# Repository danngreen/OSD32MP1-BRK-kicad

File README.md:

## OSD32MP1-BRK Kicad project

This is a Kicad project for the OSD32MP1-BRK breakout board from Octavo Systems. 
It requires Kicad v5.99 or later (aka Kicad 6). 

I converted the Altium project files for this board as best I could, using Kicad's built-in Altium importer.
The Kicad project here passes ERC and DRC, and has sane project settings (track thickness, clearance, etc.). You can view the steps I had to take to manually correct the automatic import script by viewing the git commit log.

The symbols and footprints are all extracted from the Altium project.

There are some minor font differences on the silk-screen layers, and the zones may have different clearances. I do not have access to the original gerbers, so I haven't compared them.
I have not produced this board (nor do I intend to), so I don't know if it even works.

#### Disclaimer:
I am in no way associated with Octavo Systems, and the files in this repository may contain errors or have issues, so I make no warranty as to anything. I also make no claims to ownership.
I believe I am allowed to publish this under the same license as the original files, but if I am incorrect then I will remove this repository.

The OSD32MP1-BRK Altium files are available on Octavo Systems website [here](https://octavosystems.com/octavo_products/osd32mp1-brk/#Design%20Files).

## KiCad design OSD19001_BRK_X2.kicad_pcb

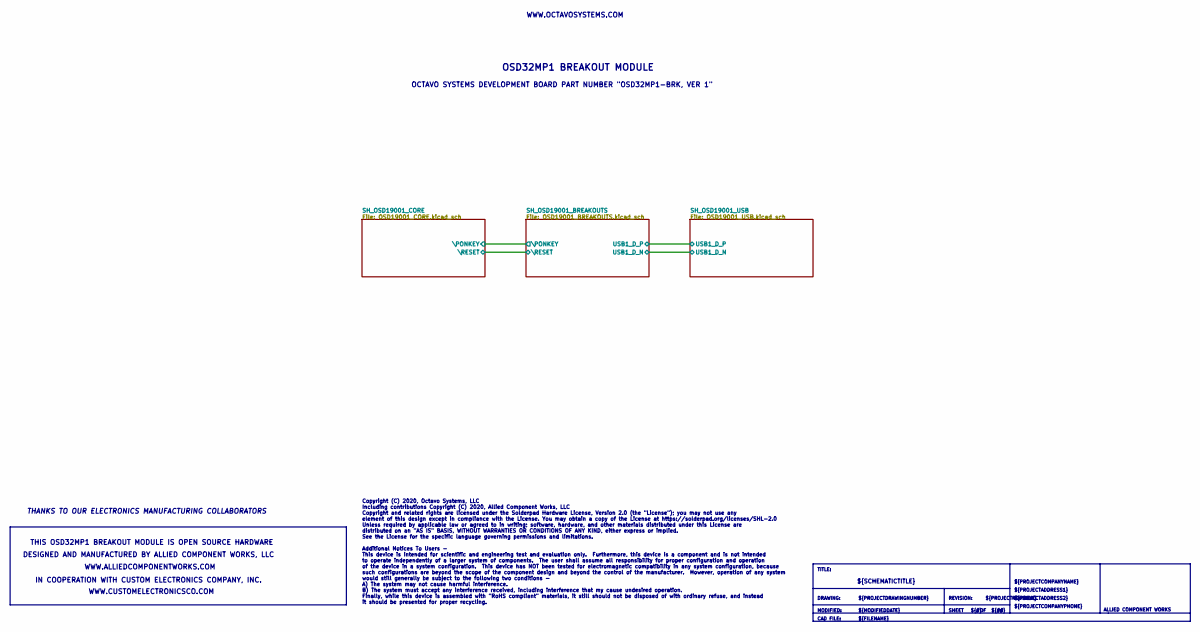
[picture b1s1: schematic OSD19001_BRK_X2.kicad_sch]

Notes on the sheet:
DESIGNED AND MANUFACTURED BY ALLIED COMPONENT WORKS, LLC
THANKS TO OUR ELECTRONICS MANUFACTURING COLLABORATORS
THIS OSD32MP1 BREAKOUT MODULE IS OPEN SOURCE HARDWARE
IN COOPERATION WITH CUSTOM ELECTRONICS COMPANY, INC.
WWW.ALLIEDCOMPONENTWORKS.COM
WWW.CUSTOMELECTRONICSCO.COM
Copyright (C) 2020, Octavo Systems, LLC Including contributions Copyright (C) 2020, Allied Component Works, LLC Copyright and related rights are licensed under the Solderpad Hardware License, Version 2.0 (the "License"); you may not use any element of this design except in compliance with the Licen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
OCTAVO SYSTEMS DEVELOPMENT BOARD PART NUMBER "OSD32MP1-BRK, VER 1"
OSD32MP1 BREAKOUT MODULE
WWW.OCTAVOSYSTEMS.COM
TITLE:
DRAWING:
MODIFIED:
CAD FILE:
${PROJECTDRAWINGNUMBER}
${MODIFIEDDATE}
${FILENAME}
${SCHEMATICTITLE}
REVISION:
SHEET
${#}
${PROJECTREVISION}
${##}
${PROJECTCOMPANYNAME}
${PROJECTADDRESS1}
${PROJECTADDRESS2}
${PROJECTCOMPANYPHONE}
ALLIED COMPONENT WORKS

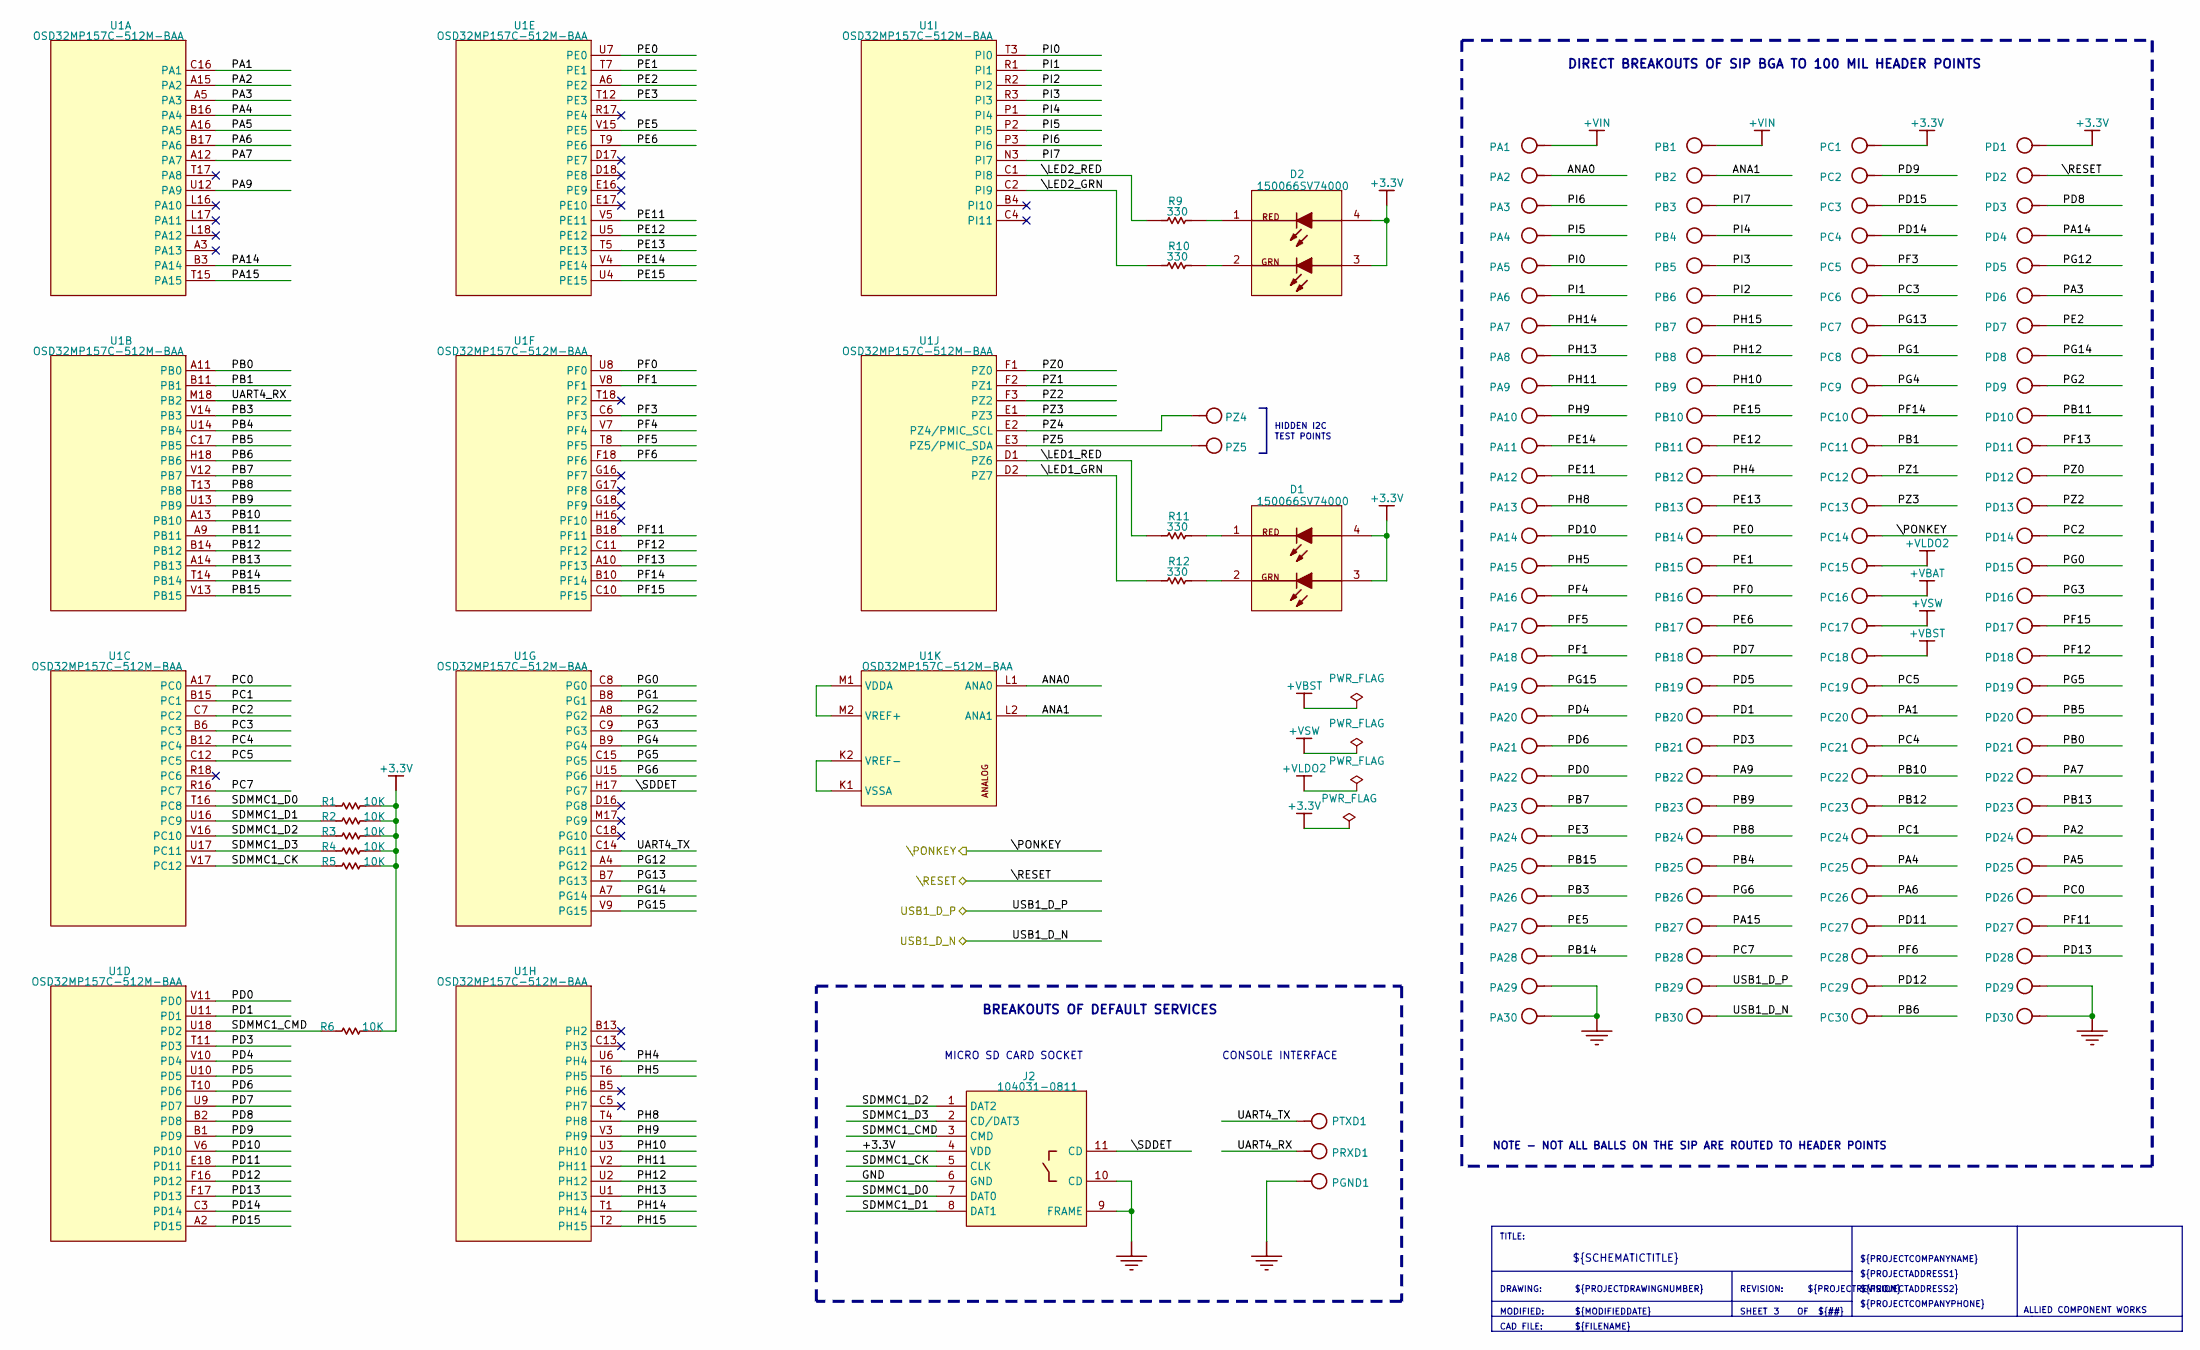
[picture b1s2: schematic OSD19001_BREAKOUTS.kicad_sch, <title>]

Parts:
D1, D2: 150066SV74000; WURTH_DUAL_0606; PARTNUMBER 150066SV74000
J2: 104031-0811; MOLEX_104031-0811; PARTNUMBER 104031-0811
PA1, PA2, PA3, PA4, PA5, PA6, PA7, PA8, PA9, PA10, PA11, PA12, PA13, PA14, PA15, PA16, PA17, PA18, PA19, PA20, PA21, PA22, PA23, PA24, PA25, PA26, PA27, PA28, PA29, PA30: TP; LP_TESTPOINT_TH
PB1, PB2, PB3, PB4, PB5, PB6, PB7, PB8, PB9, PB10, PB11, PB12, PB13, PB14, PB15, PB16, PB17, PB18, PB19, PB20, PB21, PB22, PB23, PB24, PB25, PB26, PB27, PB28, PB29, PB30: TP; LP_TESTPOINT_TH
PC1, PC2, PC3, PC4, PC5, PC6, PC7, PC8, PC9, PC10, PC11, PC12, PC13, PC14, PC15, PC16, PC17, PC18, PC19, PC20, PC21, PC22, PC23, PC24, PC25, PC26, PC27, PC28, PC29, PC30: TP; LP_TESTPOINT_TH
PD1, PD2, PD3, PD4, PD5, PD6, PD7, PD8, PD9, PD10, PD11, PD12, PD13, PD14, PD15, PD16, PD17, PD18, PD19, PD20, PD21, PD22, PD23, PD24, PD25, PD26, PD27, PD28, PD29, PD30: TP; LP_TESTPOINT_TH
PGND1: TP; LP_TESTPOINT_TH
PRXD1: TP; LP_TESTPOINT_TH
PTXD1: TP; LP_TESTPOINT_TH
PZ4, PZ5: TP; LP_TESTPOINT_SMT
R1, R2, R3, R4, R5, R6: 10K; LP_0402_LOW; TOLERANCE 5%; VOLTAGE 50V
R9, R10, R11, R12: 330; LP_0402_LOW; TOLERANCE 5%; VOLTAGE 50V
U1: OSD32MP157C-512M-BAA; BGA_OCTAVO_SIP_OSD32MP157C; PARTNUMBER OSD32MP157C-512M-BAA

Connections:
+3.3V: D1.3 (A), D1.4 (A), D2.3 (A), D2.4 (A), J2.4 (VDD), PC1.1, PD1.1, R1.2, R2.2, R3.2, R4.2, R5.2, R6.2; also elsewhere on the board
+VBAT: PC16.1; also elsewhere on the board
+VBST: PC18.1; also elsewhere on the board
+VIN: PA1.1, PB1.1; also elsewhere on the board
+VLDO2: PC15.1; also elsewhere on the board
+VSW: PC17.1; also elsewhere on the board
/SH_OSD19001_BREAKOUTS/ANA0: PA2.1, U1.L1 (ANA0)
/SH_OSD19001_BREAKOUTS/ANA1: PB2.1, U1.L2 (ANA1)
/SH_OSD19001_BREAKOUTS/PA1: PC20.1, U1.C16 (PA1)
/SH_OSD19001_BREAKOUTS/PA2: PD24.1, U1.A15 (PA2)
/SH_OSD19001_BREAKOUTS/PA3: PD6.1, U1.A5 (PA3)
/SH_OSD19001_BREAKOUTS/PA4: PC25.1, U1.B16 (PA4)
/SH_OSD19001_BREAKOUTS/PA5: PD25.1, U1.A16 (PA5)
/SH_OSD19001_BREAKOUTS/PA6: PC26.1, U1.B17 (PA6)
/SH_OSD19001_BREAKOUTS/PA7: PD22.1, U1.A12 (PA7)
/SH_OSD19001_BREAKOUTS/PA9: PB22.1, U1.U12 (PA9)
/SH_OSD19001_BREAKOUTS/PA14: PD4.1, U1.B3 (PA14)
/SH_OSD19001_BREAKOUTS/PA15: PB27.1, U1.T15 (PA15)
/SH_OSD19001_BREAKOUTS/PB0: PD21.1, U1.A11 (PB0)
/SH_OSD19001_BREAKOUTS/PB1: PC11.1, U1.B11 (PB1)
/SH_OSD19001_BREAKOUTS/PB3: PA26.1, U1.V14 (PB3)
/SH_OSD19001_BREAKOUTS/PB4: PB25.1, U1.U14 (PB4)
/SH_OSD19001_BREAKOUTS/PB5: PD20.1, U1.C17 (PB5)
/SH_OSD19001_BREAKOUTS/PB6: PC30.1, U1.H18 (PB6)
/SH_OSD19001_BREAKOUTS/PB7: PA23.1, U1.V12 (PB7)
/SH_OSD19001_BREAKOUTS/PB8: PB24.1, U1.T13 (PB8)
/SH_OSD19001_BREAKOUTS/PB9: PB23.1, U1.U13 (PB9)
/SH_OSD19001_BREAKOUTS/PB10: PC22.1, U1.A13 (PB10)
/SH_OSD19001_BREAKOUTS/PB11: PD10.1, U1.A9 (PB11)
/SH_OSD19001_BREAKOUTS/PB12: PC23.1, U1.B14 (PB12)
/SH_OSD19001_BREAKOUTS/PB13: PD23.1, U1.A14 (PB13)
/SH_OSD19001_BREAKOUTS/PB14: PA28.1, U1.T14 (PB14)
/SH_OSD19001_BREAKOUTS/PB15: PA25.1, U1.V13 (PB15)
/SH_OSD19001_BREAKOUTS/PC0: PD26.1, U1.A17 (PC0)
/SH_OSD19001_BREAKOUTS/PC1: PC24.1, U1.B15 (PC1)
/SH_OSD19001_BREAKOUTS/PC2: PD14.1, U1.C7 (PC2)
/SH_OSD19001_BREAKOUTS/PC3: PC6.1, U1.B6 (PC3)
/SH_OSD19001_BREAKOUTS/PC4: PC21.1, U1.B12 (PC4)
/SH_OSD19001_BREAKOUTS/PC5: PC19.1, U1.C12 (PC5)
/SH_OSD19001_BREAKOUTS/PC7: PB28.1, U1.R16 (PC7)
/SH_OSD19001_BREAKOUTS/PD0: PA22.1, U1.V11 (PD0)
/SH_OSD19001_BREAKOUTS/PD1: PB20.1, U1.U11 (PD1)
/SH_OSD19001_BREAKOUTS/PD3: PB21.1, U1.T11 (PD3)
/SH_OSD19001_BREAKOUTS/PD4: PA20.1, U1.V10 (PD4)
/SH_OSD19001_BREAKOUTS/PD5: PB19.1, U1.U10 (PD5)
/SH_OSD19001_BREAKOUTS/PD6: PA21.1, U1.T10 (PD6)
/SH_OSD19001_BREAKOUTS/PD7: PB18.1, U1.U9 (PD7)
/SH_OSD19001_BREAKOUTS/PD8: PD3.1, U1.B2 (PD8)
/SH_OSD19001_BREAKOUTS/PD9: PC2.1, U1.B1 (PD9)
/SH_OSD19001_BREAKOUTS/PD10: PA14.1, U1.V6 (PD10)
/SH_OSD19001_BREAKOUTS/PD11: PC27.1, U1.E18 (PD11)
/SH_OSD19001_BREAKOUTS/PD12: PC29.1, U1.F16 (PD12)
/SH_OSD19001_BREAKOUTS/PD13: PD28.1, U1.F17 (PD13)
/SH_OSD19001_BREAKOUTS/PD14: PC4.1, U1.C3 (PD14)
/SH_OSD19001_BREAKOUTS/PD15: PC3.1, U1.A2 (PD15)
/SH_OSD19001_BREAKOUTS/PE0: PB14.1, U1.U7 (PE0)
/SH_OSD19001_BREAKOUTS/PE1: PB15.1, U1.T7 (PE1)
/SH_OSD19001_BREAKOUTS/PE2: PD7.1, U1.A6 (PE2)
/SH_OSD19001_BREAKOUTS/PE3: PA24.1, U1.T12 (PE3)
/SH_OSD19001_BREAKOUTS/PE5: PA27.1, U1.V15 (PE5)
/SH_OSD19001_BREAKOUTS/PE6: PB17.1, U1.T9 (PE6)
/SH_OSD19001_BREAKOUTS/PE11: PA12.1, U1.V5 (PE11)
/SH_OSD19001_BREAKOUTS/PE12: PB11.1, U1.U5 (PE12)
/SH_OSD19001_BREAKOUTS/PE13: PB13.1, U1.T5 (PE13)
/SH_OSD19001_BREAKOUTS/PE14: PA11.1, U1.V4 (PE14)
/SH_OSD19001_BREAKOUTS/PE15: PB10.1, U1.U4 (PE15)
/SH_OSD19001_BREAKOUTS/PF0: PB16.1, U1.U8 (PF0)
/SH_OSD19001_BREAKOUTS/PF1: PA18.1, U1.V8 (PF1)
/SH_OSD19001_BREAKOUTS/PF3: PC5.1, U1.C6 (PF3)
/SH_OSD19001_BREAKOUTS/PF4: PA16.1, U1.V7 (PF4)
/SH_OSD19001_BREAKOUTS/PF5: PA17.1, U1.T8 (PF5)
/SH_OSD19001_BREAKOUTS/PF6: PC28.1, U1.F18 (PF6)
/SH_OSD19001_BREAKOUTS/PF11: PD27.1, U1.B18 (PF11)
/SH_OSD19001_BREAKOUTS/PF12: PD18.1, U1.C11 (PF12)
/SH_OSD19001_BREAKOUTS/PF13: PD11.1, U1.A10 (PF13)
/SH_OSD19001_BREAKOUTS/PF14: PC10.1, U1.B10 (PF14)
/SH_OSD19001_BREAKOUTS/PF15: PD17.1, U1.C10 (PF15)
/SH_OSD19001_BREAKOUTS/PG0: PD15.1, U1.C8 (PG0)
/SH_OSD19001_BREAKOUTS/PG1: PC8.1, U1.B8 (PG1)
/SH_OSD19001_BREAKOUTS/PG2: PD9.1, U1.A8 (PG2)
/SH_OSD19001_BREAKOUTS/PG3: PD16.1, U1.C9 (PG3)
/SH_OSD19001_BREAKOUTS/PG4: PC9.1, U1.B9 (PG4)
/SH_OSD19001_BREAKOUTS/PG5: PD19.1, U1.C15 (PG5)
/SH_OSD19001_BREAKOUTS/PG6: PB26.1, U1.U15 (PG6)
/SH_OSD19001_BREAKOUTS/PG12: PD5.1, U1.A4 (PG12)
/SH_OSD19001_BREAKOUTS/PG13: PC7.1, U1.B7 (PG13)
/SH_OSD19001_BREAKOUTS/PG14: PD8.1, U1.A7 (PG14)
/SH_OSD19001_BREAKOUTS/PG15: PA19.1, U1.V9 (PG15)
/SH_OSD19001_BREAKOUTS/PH4: PB12.1, U1.U6 (PH4)
/SH_OSD19001_BREAKOUTS/PH5: PA15.1, U1.T6 (PH5)
/SH_OSD19001_BREAKOUTS/PH8: PA13.1, U1.T4 (PH8)
/SH_OSD19001_BREAKOUTS/PH9: PA10.1, U1.V3 (PH9)
/SH_OSD19001_BREAKOUTS/PH10: PB9.1, U1.U3 (PH10)
/SH_OSD19001_BREAKOUTS/PH11: PA9.1, U1.V2 (PH11)
/SH_OSD19001_BREAKOUTS/PH12: PB8.1, U1.U2 (PH12)
/SH_OSD19001_BREAKOUTS/PH13: PA8.1, U1.U1 (PH13)
/SH_OSD19001_BREAKOUTS/PH14: PA7.1, U1.T1 (PH14)
/SH_OSD19001_BREAKOUTS/PH15: PB7.1, U1.T2 (PH15)
/SH_OSD19001_BREAKOUTS/PI0: PA5.1, U1.T3 (PI0)
/SH_OSD19001_BREAKOUTS/PI1: PA6.1, U1.R1 (PI1)
/SH_OSD19001_BREAKOUTS/PI2: PB6.1, U1.R2 (PI2)
/SH_OSD19001_BREAKOUTS/PI3: PB5.1, U1.R3 (PI3)
/SH_OSD19001_BREAKOUTS/PI4: PB4.1, U1.P1 (PI4)
/SH_OSD19001_BREAKOUTS/PI5: PA4.1, U1.P2 (PI5)
/SH_OSD19001_BREAKOUTS/PI6: PA3.1, U1.P3 (PI6)
/SH_OSD19001_BREAKOUTS/PI7: PB3.1, U1.N3 (PI7)
/SH_OSD19001_BREAKOUTS/PZ0: PD12.1, U1.F1 (PZ0)
/SH_OSD19001_BREAKOUTS/PZ1: PC12.1, U1.F2 (PZ1)
/SH_OSD19001_BREAKOUTS/PZ2: PD13.1, U1.F3 (PZ2)
/SH_OSD19001_BREAKOUTS/PZ3: PC13.1, U1.E1 (PZ3)
/SH_OSD19001_BREAKOUTS/PZ4: PZ4.1, U1.E2 (PZ4/PMIC_SCL)
/SH_OSD19001_BREAKOUTS/PZ5: PZ5.1, U1.E3 (PZ5/PMIC_SDA)
/SH_OSD19001_BREAKOUTS/SDMMC1_CK: J2.5 (CLK), R5.1, U1.V17 (PC12)
/SH_OSD19001_BREAKOUTS/SDMMC1_CMD: J2.3 (CMD), R6.1, U1.U18 (PD2)
/SH_OSD19001_BREAKOUTS/SDMMC1_D0: J2.7 (DAT0), R1.1, U1.T16 (PC8)
/SH_OSD19001_BREAKOUTS/SDMMC1_D1: J2.8 (DAT1), R2.1, U1.U16 (PC9)
/SH_OSD19001_BREAKOUTS/SDMMC1_D2: J2.1 (DAT2), R3.1, U1.V16 (PC10)
/SH_OSD19001_BREAKOUTS/SDMMC1_D3: J2.2 (CD/DAT3), R4.1, U1.U17 (PC11)
/SH_OSD19001_BREAKOUTS/UART4_RX: PRXD1.1, U1.M18 (PB2)
/SH_OSD19001_BREAKOUTS/UART4_TX: PTXD1.1, U1.C14 (PG11)
/SH_OSD19001_BREAKOUTS/USB1_D_N: PB30.1; also elsewhere on the board
/SH_OSD19001_BREAKOUTS/USB1_D_P: PB29.1; also elsewhere on the board
/SH_OSD19001_BREAKOUTS/\LED1_GRN: R12.1, U1.D2 (PZ7)
/SH_OSD19001_BREAKOUTS/\LED1_RED: R11.1, U1.D1 (PZ6)
/SH_OSD19001_BREAKOUTS/\LED2_GRN: R10.1, U1.C2 (PI9)
/SH_OSD19001_BREAKOUTS/\LED2_RED: R9.1, U1.C1 (PI8)
/SH_OSD19001_BREAKOUTS/\PONKEY: PC14.1; also elsewhere on the board
/SH_OSD19001_BREAKOUTS/\RESET: PD2.1; also elsewhere on the board
/SH_OSD19001_BREAKOUTS/\SDDET: J2.11 (CD), U1.H17 (PG7)
GND: J2.6 (GND), J2.9 (FRAME), J2.10 (CD), PA29.1, PA30.1, PD29.1, PD30.1, PGND1.1; also elsewhere on the board
unnamed: D1.1 (K), R11.2
unnamed: D1.2 (K), R12.2
unnamed: D2.1 (K), R9.2
unnamed: D2.2 (K), R10.2
unnamed: U1.K1 (VSSA), U1.K2 (VREF-)
unnamed: U1.M1 (VDDA), U1.M2 (VREF+)

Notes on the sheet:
MICRO SD CARD SOCKET
BREAKOUTS OF DEFAULT SERVICES
CONSOLE INTERFACE
HIDDEN I2C
TEST POINTS
NOTE - NOT ALL BALLS ON THE SIP ARE ROUTED TO HEADER POINTS
TITLE:
DRAWING:
MODIFIED:
CAD FILE:
DIRECT BREAKOUTS OF SIP BGA TO 100 MIL HEADER POINTS
${PROJECTDRAWINGNUMBER}
${MODIFIEDDATE}
${FILENAME}
${SCHEMATICTITLE}
REVISION:
SHEET
${PROJECTREVISION}
${##}
${PROJECTCOMPANYNAME}
${PROJECTADDRESS1}
${PROJECTADDRESS2}
${PROJECTCOMPANYPHONE}
ALLIED COMPONENT WORKS

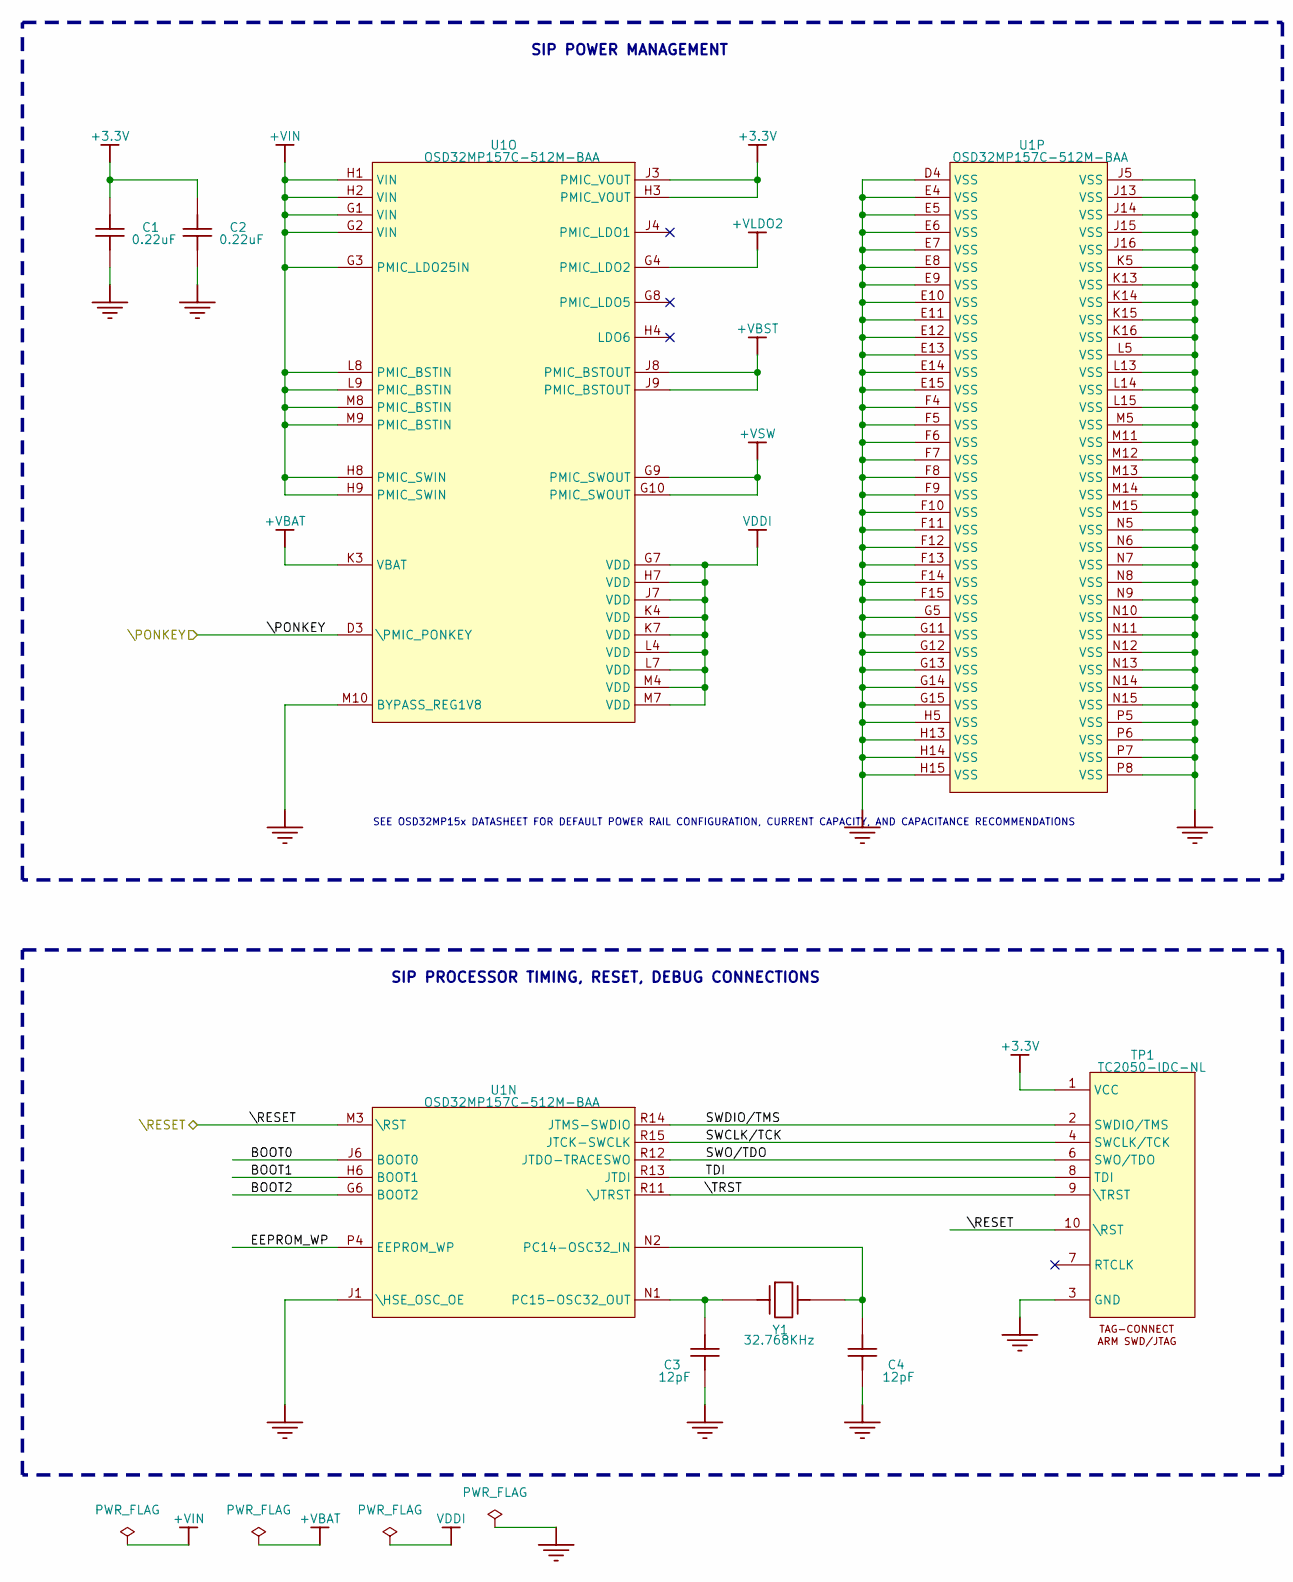
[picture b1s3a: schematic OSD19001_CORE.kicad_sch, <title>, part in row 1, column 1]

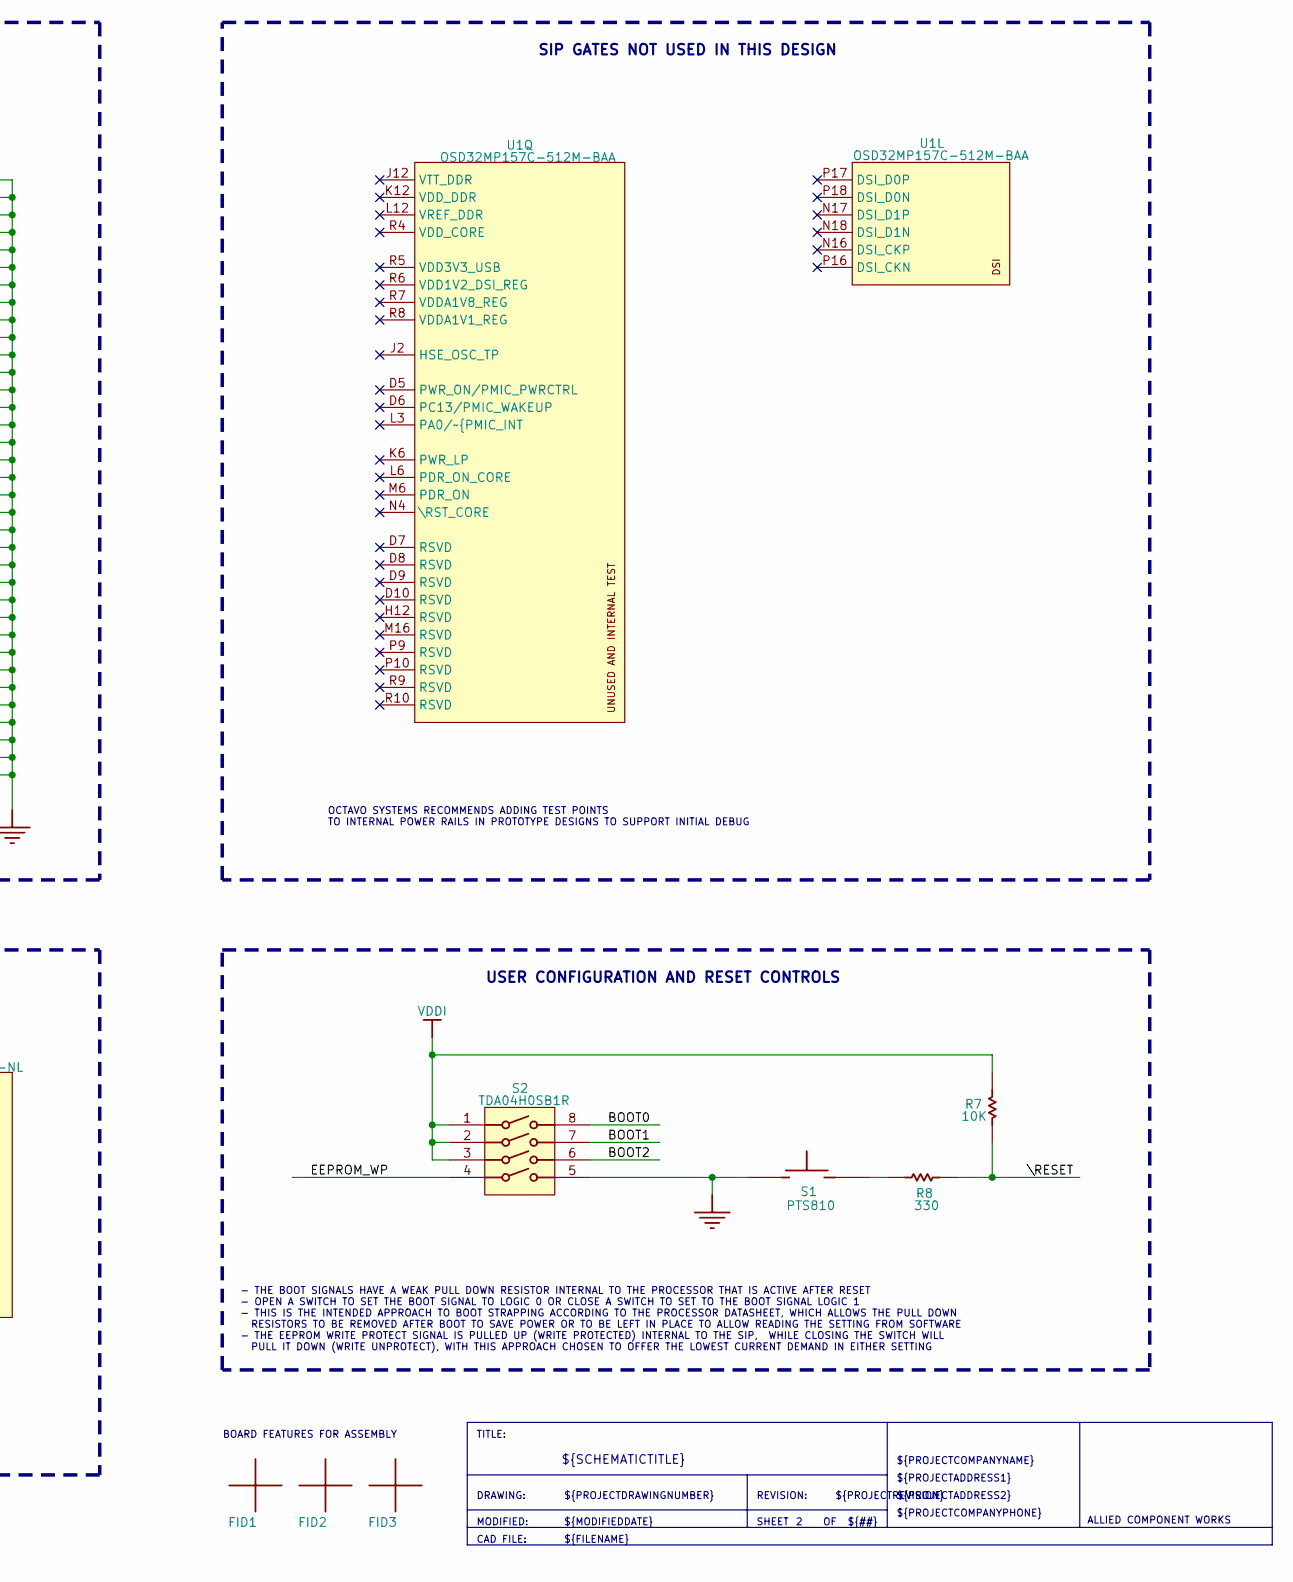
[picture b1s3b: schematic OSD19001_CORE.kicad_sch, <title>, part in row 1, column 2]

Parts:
C1, C2: 0.22uF; LP_0603_HIGH; TOLERANCE 10%; VOLTAGE 25V
C3, C4: 12pF; LP_0402_HIGH; TOLERANCE 10%; VOLTAGE 25V; PARTNUMBER *
FID1, FID2, FID3: FID; FID_ROUND_40_TOP
R7: 10K; LP_0402_LOW; TOLERANCE 5%; VOLTAGE 50V
R8: 330; LP_0402_LOW; TOLERANCE 5%; VOLTAGE 50V
S1: PTS810; C&K_PTS810; PARTNUMBER PTS810
S2: TDA04H0SB1R; C&K_TDA04; PARTNUMBER TDA04H0SB1R
TP1: TC2050-IDC-NL; TC2050_SITE_NL; PARTNUMBER TC2050-IDC-NL
U1: OSD32MP157C-512M-BAA; BGA_OCTAVO_SIP_OSD32MP157C; PARTNUMBER OSD32MP157C-512M-BAA
Y1: 32.768KHz; NDK_CRYSTAL_1.5X3.2; PARTNUMBER NX3215SA-32.768K-STD-MUA-9

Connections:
+3.3V: C1.1, C2.1, TP1.1 (VCC), U1.H3 (PMIC_VOUT), U1.J3 (PMIC_VOUT); also elsewhere on the board
+VBAT: U1.K3 (VBAT); also elsewhere on the board
+VBST: U1.J8 (PMIC_BSTOUT), U1.J9 (PMIC_BSTOUT); also elsewhere on the board
+VIN: U1.G1 (VIN), U1.G2 (VIN), U1.G3 (PMIC_LDO25IN), U1.H1 (VIN), U1.H2 (VIN), U1.H8 (PMIC_SWIN), U1.H9 (PMIC_SWIN), U1.L8 (PMIC_BSTIN), U1.L9 (PMIC_BSTIN), U1.M8 (PMIC_BSTIN), U1.M9 (PMIC_BSTIN); also elsewhere on the board
+VLDO2: U1.G4 (PMIC_LDO2); also elsewhere on the board
+VSW: U1.G9 (PMIC_SWOUT), U1.G10 (PMIC_SWOUT); also elsewhere on the board
/SH_OSD19001_BREAKOUTS/\PONKEY: U1.D3 (\PMIC_PONKEY); also elsewhere on the board
/SH_OSD19001_BREAKOUTS/\RESET: R7.1, R8.2, TP1.10 (\RST), U1.M3 (\RST); also elsewhere on the board
/SH_OSD19001_CORE/BOOT0: S2.8, U1.J6 (BOOT0)
/SH_OSD19001_CORE/BOOT1: S2.7, U1.H6 (BOOT1)
/SH_OSD19001_CORE/BOOT2: S2.6, U1.G6 (BOOT2)
/SH_OSD19001_CORE/EEPROM_WP: S2.4, U1.P4 (EEPROM_WP)
/SH_OSD19001_CORE/SWCLK/TCK: TP1.4 (SWCLK/TCK), U1.R15 (JTCK-SWCLK)
/SH_OSD19001_CORE/SWDIO/TMS: TP1.2 (SWDIO/TMS), U1.R14 (JTMS-SWDIO)
/SH_OSD19001_CORE/SWO/TDO: TP1.6 (SWO/TDO), U1.R12 (JTDO-TRACESWO)
/SH_OSD19001_CORE/TDI: TP1.8 (TDI), U1.R13 (JTDI)
/SH_OSD19001_CORE/\TRST: TP1.9 (\TRST), U1.R11 (\JTRST)
GND: C1.2, C2.2, C3.2, C4.2, S1.2, S2.5, TP1.3 (GND), U1.D4 (VSS), U1.E4 (VSS), U1.E5 (VSS), U1.E6 (VSS), U1.E7 (VSS), U1.E8 (VSS), U1.E9 (VSS), U1.E10 (VSS), U1.E11 (VSS), U1.E12 (VSS), U1.E13 (VSS), U1.E14 (VSS), U1.E15 (VSS), U1.F4 (VSS), U1.F5 (VSS), U1.F6 (VSS), U1.F7 (VSS), U1.F8 (VSS), U1.F9 (VSS), U1.F10 (VSS), U1.F11 (VSS), U1.F12 (VSS), U1.F13 (VSS), U1.F14 (VSS), U1.F15 (VSS), U1.G5 (VSS), U1.G11 (VSS), U1.G12 (VSS), U1.G13 (VSS), U1.G14 (VSS), U1.G15 (VSS), U1.H5 (VSS), U1.H13 (VSS), U1.H14 (VSS), U1.H15 (VSS), U1.J1 (\HSE_OSC_OE), U1.J5 (VSS), U1.J13 (VSS), U1.J14 (VSS), U1.J15 (VSS), U1.J16 (VSS), U1.K5 (VSS), U1.K13 (VSS), U1.K14 (VSS), U1.K15 (VSS), U1.K16 (VSS), U1.L5 (VSS), U1.L13 (VSS), U1.L14 (VSS), U1.L15 (VSS), U1.M5 (VSS), U1.M10 (BYPASS_REG1V8), U1.M11 (VSS), U1.M12 (VSS), U1.M13 (VSS), U1.M14 (VSS), U1.M15 (VSS), U1.N5 (VSS), U1.N6 (VSS), U1.N7 (VSS), U1.N8 (VSS), U1.N9 (VSS), U1.N10 (VSS), U1.N11 (VSS), U1.N12 (VSS), U1.N13 (VSS), U1.N14 (VSS), U1.N15 (VSS), U1.P5 (VSS), U1.P6 (VSS), U1.P7 (VSS), U1.P8 (VSS); also elsewhere on the board
unnamed: C3.1, U1.N1 (PC15-OSC32_OUT), Y1.2
unnamed: C4.1, U1.N2 (PC14-OSC32_IN), Y1.1
unnamed: R8.1, S1.1
VDDI: R7.2, S2.1, S2.2, S2.3, U1.G7 (VDD), U1.H7 (VDD), U1.J7 (VDD), U1.K4 (VDD), U1.K7 (VDD), U1.L4 (VDD), U1.L7 (VDD), U1.M4 (VDD), U1.M7 (VDD)

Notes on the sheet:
SEE OSD32MP15x DATASHEET FOR DEFAULT POWER RAIL CONFIGURATION, CURRENT CAPACITY, AND CAPACITANCE RECOMMENDATIONS
SIP PROCESSOR TIMING, RESET, DEBUG CONNECTIONS
SIP POWER MANAGEMENT
BOARD FEATURES FOR ASSEMBLY
- THE BOOT SIGNALS HAVE A WEAK PULL DOWN RESISTOR INTERNAL TO THE PROCESSOR THAT IS ACTIVE AFTER RESET - OPEN A SWITCH TO SET THE BOOT SIGNAL TO LOGIC 0 OR CLOSE A SWITCH TO SET TO THE BOOT SIGNAL LOGIC 1 - THIS IS THE INTENDED APPROACH TO BOOT STRAPPING ACCORDING TO THE PROCESSOR DATASHEET, WHICH 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
OCTAVO SYSTEMS RECOMMENDS ADDING TEST POINTS TO INTERNAL POWER RAILS IN PROTOTYPE DESIGNS TO SUPPORT INITIAL DEBUG
TITLE:
DRAWING:
MODIFIED:
CAD FILE:
USER CONFIGURATION AND RESET CONTROLS
SIP GATES NOT USED IN THIS DESIGN
${PROJECTDRAWINGNUMBER}
${MODIFIEDDATE}
${FILENAME}
${SCHEMATICTITLE}
REVISION:
SHEET
${PROJECTREVISION}
${##}
${PROJECTCOMPANYNAME}
${PROJECTADDRESS1}
${PROJECTADDRESS2}
${PROJECTCOMPANYPHONE}
ALLIED COMPONENT WORKS

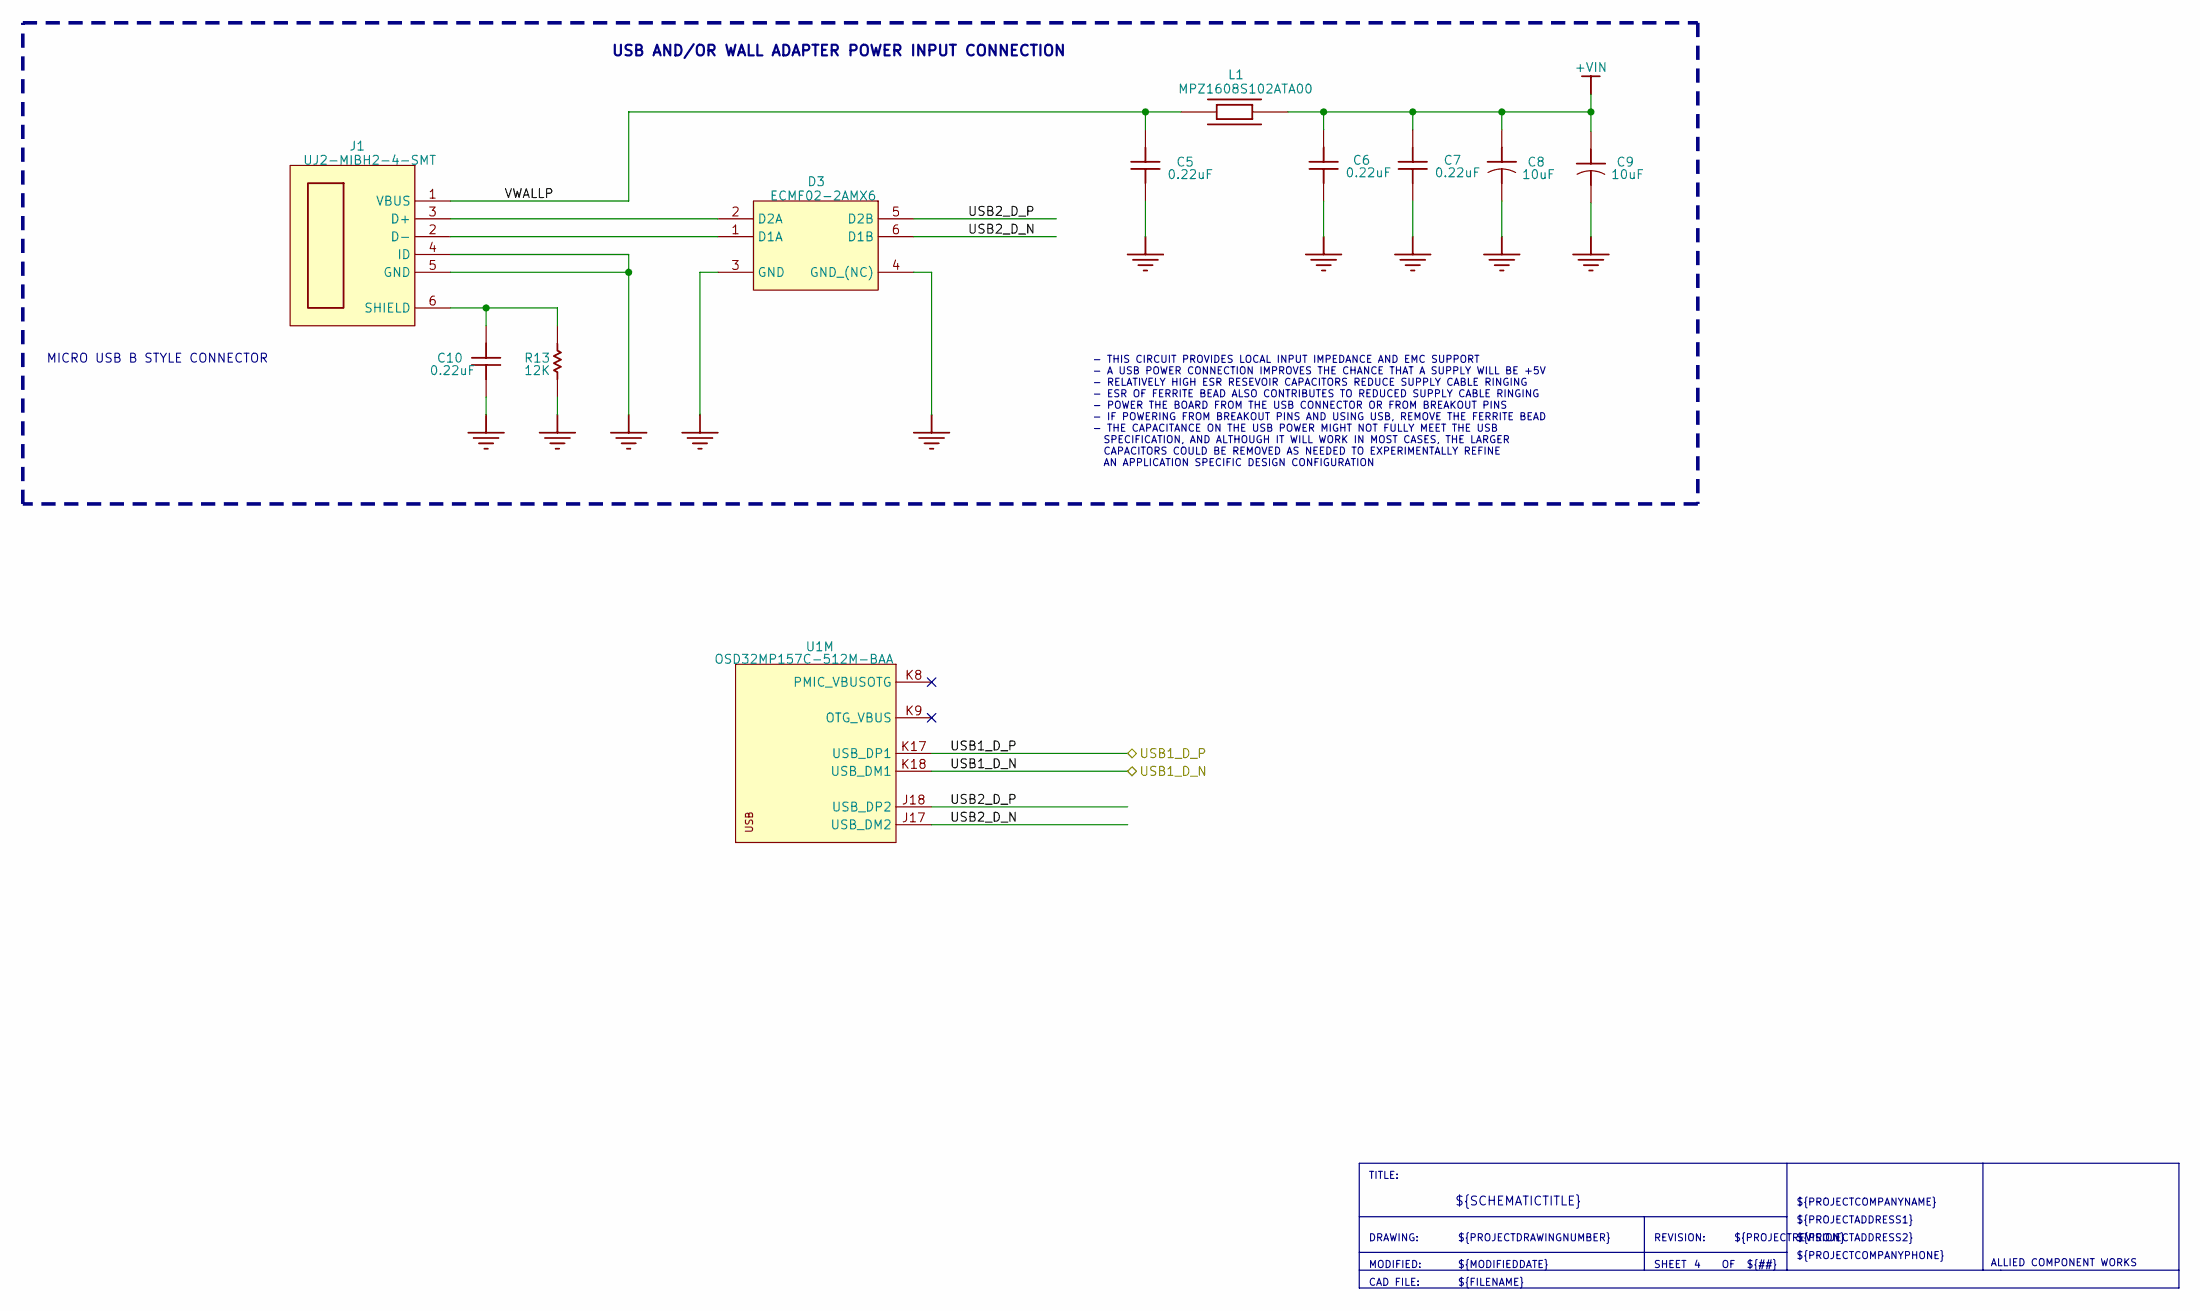
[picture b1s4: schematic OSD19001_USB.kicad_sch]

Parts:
C5, C6, C7, C10: 0.22uF; LP_0603_HIGH; TOLERANCE 10%; VOLTAGE 25V
C8, C9: 10uF; LP_EIAB; TOLERANCE 20%; VOLTAGE 10V
D3: ECMF02-2AMX6; DFN6_6L_ST; PARTNUMBER ECMF02-2AMX6
J1: UJ2-MIBH2-4-SMT; CUI_UJ2-MIBH2-4-SMT; PARTNUMBER UJ2-MIBH2-4-SMT
L1: MPZ1608S102ATA00; LP_0603_IND; PARTNUMBER MPZ1608S102ATA00
R13: 12K; LP_0603_LOW; TOLERANCE 5%; VOLTAGE 50V
U1: OSD32MP157C-512M-BAA; BGA_OCTAVO_SIP_OSD32MP157C; PARTNUMBER OSD32MP157C-512M-BAA

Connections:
+VIN: C6.2, C7.2, C8.1, C9.1, L1.2; also elsewhere on the board
/SH_OSD19001_BREAKOUTS/USB1_D_N: U1.K18 (USB_DM1); also elsewhere on the board
/SH_OSD19001_BREAKOUTS/USB1_D_P: U1.K17 (USB_DP1); also elsewhere on the board
/SH_OSD19001_USB/USB2_D_N: D3.6 (D1B), U1.J17 (USB_DM2)
/SH_OSD19001_USB/USB2_D_P: D3.5 (D2B), U1.J18 (USB_DP2)
/SH_OSD19001_USB/VWALLP: C5.2, J1.1 (VBUS), L1.1
GND: C5.1, C6.1, C7.1, C8.2, C9.2, C10.1, D3.3 (GND), D3.4 (GND_(NC)), J1.4 (ID), J1.5 (GND), R13.1; also elsewhere on the board
unnamed: C10.2, J1.6 (SHIELD), R13.2
unnamed: D3.1 (D1A), J1.2 (D-)
unnamed: D3.2 (D2A), J1.3 (D+)

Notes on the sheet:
MICRO USB B STYLE CONNECTOR
USB AND/OR WALL ADAPTER POWER INPUT CONNECTION
- THIS CIRCUIT PROVIDES LOCAL INPUT IMPEDANCE AND EMC SUPPORT - A USB POWER CONNECTION IMPROVES THE CHANCE THAT A SUPPLY WILL BE +5V - RELATIVELY HIGH ESR RESEVOIR CAPACITORS REDUCE SUPPLY CABLE RINGING - ESR OF FERRITE BEAD ALSO CONTRIBUTES TO REDUCED SUPPLY CABLE RINGING - POWER THE BOARD FROM TH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
TITLE:
DRAWING:
MODIFIED:
CAD FILE:
${PROJECTDRAWINGNUMBER}
${MODIFIEDDATE}
${FILENAME}
${SCHEMATICTITLE}
REVISION:
SHEET
${PROJECTREVISION}
${##}
${PROJECTCOMPANYNAME}
${PROJECTADDRESS1}
${PROJECTADDRESS2}
${PROJECTCOMPANYPHONE}
ALLIED COMPONENT WORKS

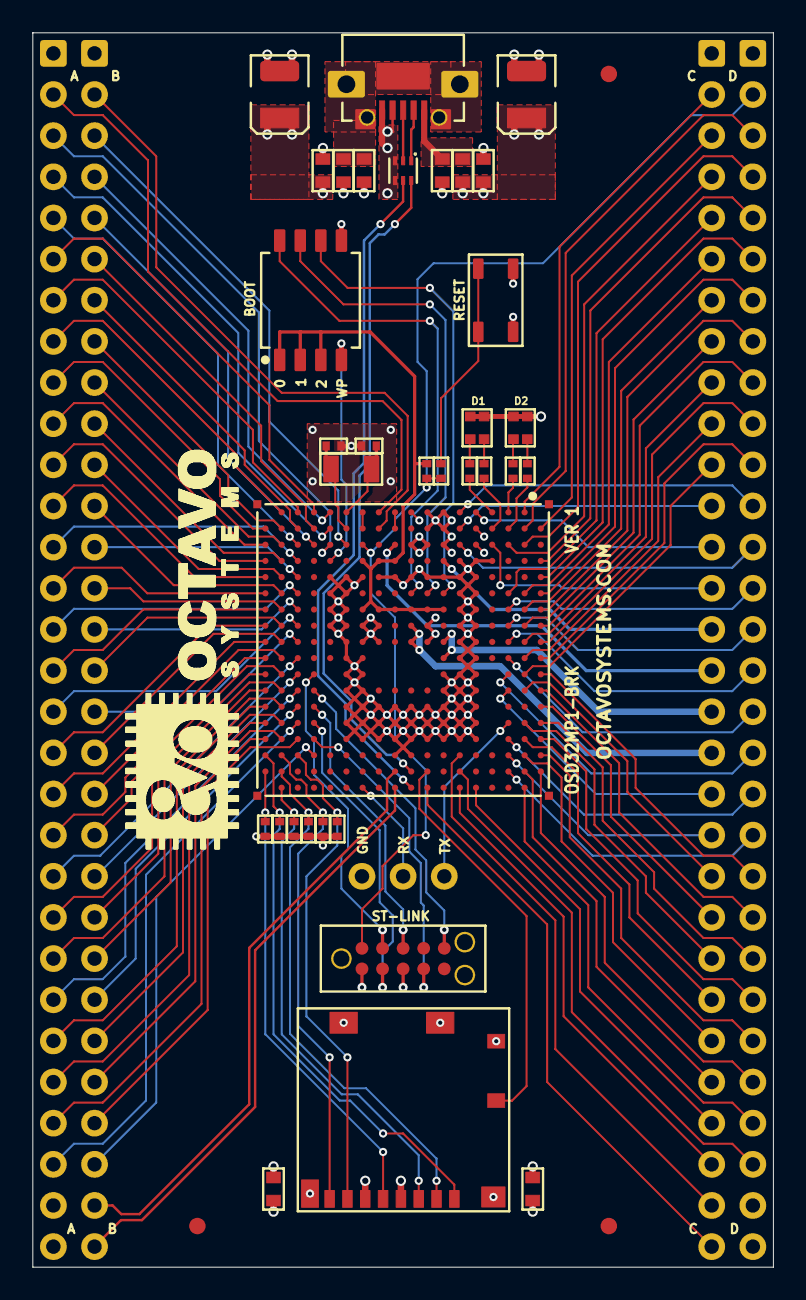
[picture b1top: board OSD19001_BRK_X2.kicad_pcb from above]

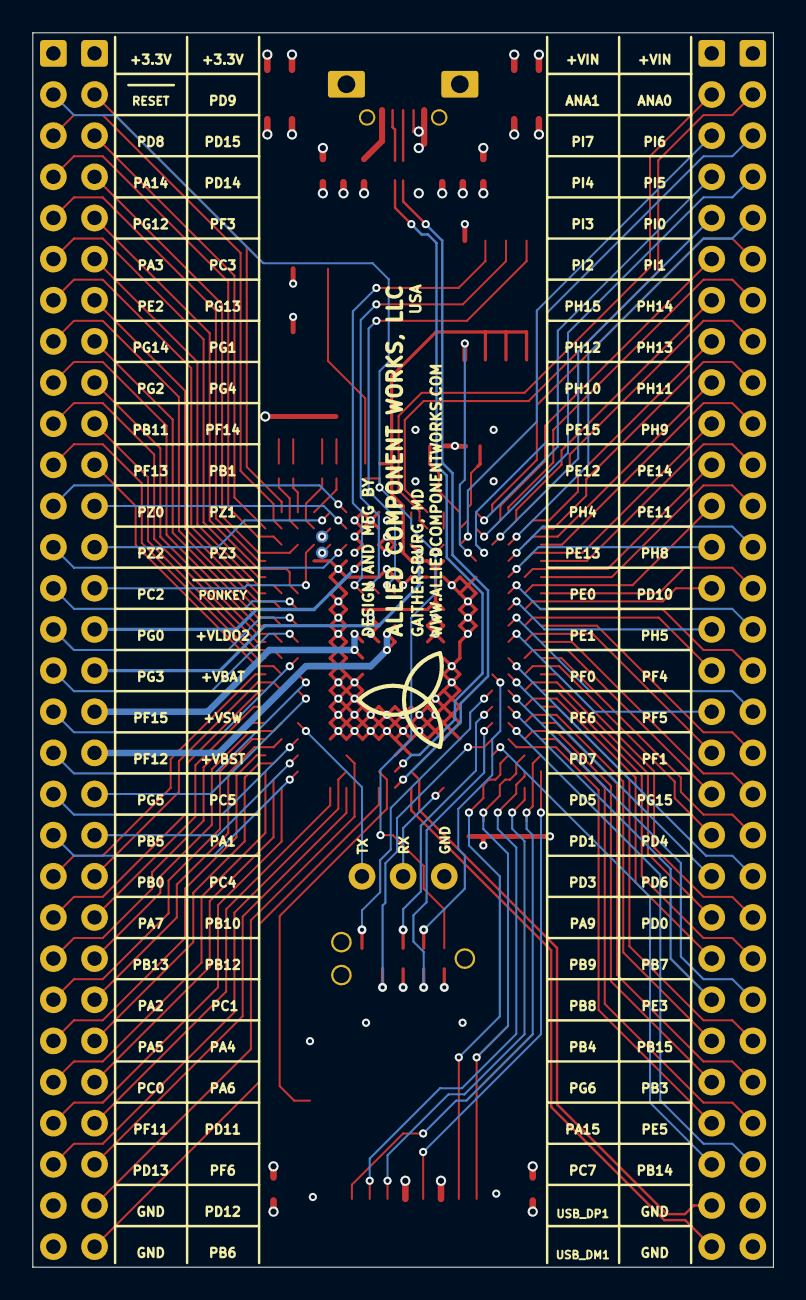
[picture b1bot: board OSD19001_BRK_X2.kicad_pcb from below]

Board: 4 copper layers, 45.7 x 76.2 mm, 162 parts (2 on the bottom side), 155 nets.

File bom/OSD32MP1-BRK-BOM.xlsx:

Item | Qty | Part Number | Part Description | Manufacturer | Reference Designator
1 | 1 |  | PWB, OSD19001_BRK_X2 | Variable
2 | 1 | UJ2-MIBH2-4-SMT | Connector, USB Micro B, RA | CUI | J1
3 | 1 | 104031-0811 | Connector, SD Card, Push-Pull | Molex | J2
4 | 1 | PTS810-SJK-250-SMTR-LFS | Switch, Tact, Vertical | C&K | S1
5 | 1 | TDA04H0SB1R | Switch, DIP, 4-Postion, SO | C&K | S2
6 | 1 | OSD32MP157C-512M-BAA | IC, Processor Subsystem SIP, BGA | Octavo Systems | U1
7 | 2 | 150066SV74000 | Diode, LED Indicator, Red/Green, 0606 | Wurth | D1, D2
8 | 1 | ECMF02-2AMX6 | Diode, USB Protection And Filter, DFN | STMicroelectronics | D3
9 | 1 | MPZ1608S102ATA00 | Inductor, Ferrite Bead, 0.8A, 1K Ohm, 0603 | TDK | L1
10 | 1 | NX3215SA-32.768K-STD-MUA-9 | Crystal, 32.768KHz, 9pF, 1206 | NDK | Y1
11 | 5 |  | Resistor, 330 Ohm, 0402 | Variable | R8-R12
12 | 7 |  | Resistor, 10K Ohm, 0402 | Variable | R1-R7
13 | 1 |  | Resistor, 12K Ohm, 0603 | Variable | R13
14 | 2 |  | Capacitor, 12pF, COG/NPO, 0402 | Variable | C3,C4
15 | 6 |  | Capacitor, 0.22uF, X5R, 0603 | Variable | C1,C2,C5-C7,C10
16 | 2 |  | Capacitor, 10uF, Tantalum, EIAB | Variable | C8,C9
Count | 34
 |  | Global Notes:
 |  | This PWA (printed wiring assembly) serves as Octavo Systems part number OSD32MP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
 |  | Resistors 5% or better, unless indicated
 |  | Capacitors +80%/-20% or better, 10V or higher, unless indicated

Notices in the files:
OSD19001_BRK_X2.kicad_sch:
Unless required by applicable law or agreed to in writing; software, hardware, and other materials distributed under this License are
